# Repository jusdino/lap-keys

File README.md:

# lap-keys
A keyboard design that allows hands to naturally rest on the lap, while using

## Overview
This is a design prototype in progress for a new keyboard that will hopefully fix some ergonomic issues with my desk at home. Namely, I'm sick of keeping my hands up on a desk all day. I'd much rather let them relax on my lap while I work. Nothing I can find for commercially available (or other build-your-own) keyboard/mouse units seem to fit the bill.

## Prototypes
**Split Sixty Wedge**
- This is the first prototype I'm working on that is intended to be 'lap-friendly'. It should receive the custom PCBs I've designed to each include 5 switches in a column and a header that sticks out the top to allow for hand-wiring the key matrix between columns. This prototype is designed to be a simple 5x12 rectilinear split keyboard with each half arranged into a forward-pointing wedge. This configuration should get your wrists into a sensible orientation while typing either on a desk or your lap. It also includes a trackball, to help reduce the need for a dedicated pointing device. I'm calling this first prototype the **split sixty wedge**:

## Prints
The prints section of this repo consists of [OpenScad](https://www.openscad.org/) modules for any prototyping I'm doing and some that allow for quick definition of a keyboard with little more than the coordinates of where you want keys to be located. I've thrown together some *brain_storming* layouts with just coordinates that still produced a part that was reasonably printable, if not polished-looking. 

Some of the OpenScad modules include:

- Any prototypes I'm currently working on
- A rough mock-up of a CherryMX switch:

**Brain storming modules** that can be used for quick brain storming of layout ideas and can potentially be printed out and hand-wired:
- Sockets to fit the CherryMX switch:

- A base to hold the sockets with space underneath for wiring:

- Some utility modules that can take a set of coordinates and translate them into the start of a workable keyboard:

## Firmware
The firmware section of this repo contains MicroController Unit firmware I've designed to run on the MCU that drives the keyboard prototypes. These firmwares use the [QMK firmware](https://qmk.fm/) as their base.

## PCBs
The pcbs section of the repo contains KiCad PCB design files for any PCBs I design as part of this project

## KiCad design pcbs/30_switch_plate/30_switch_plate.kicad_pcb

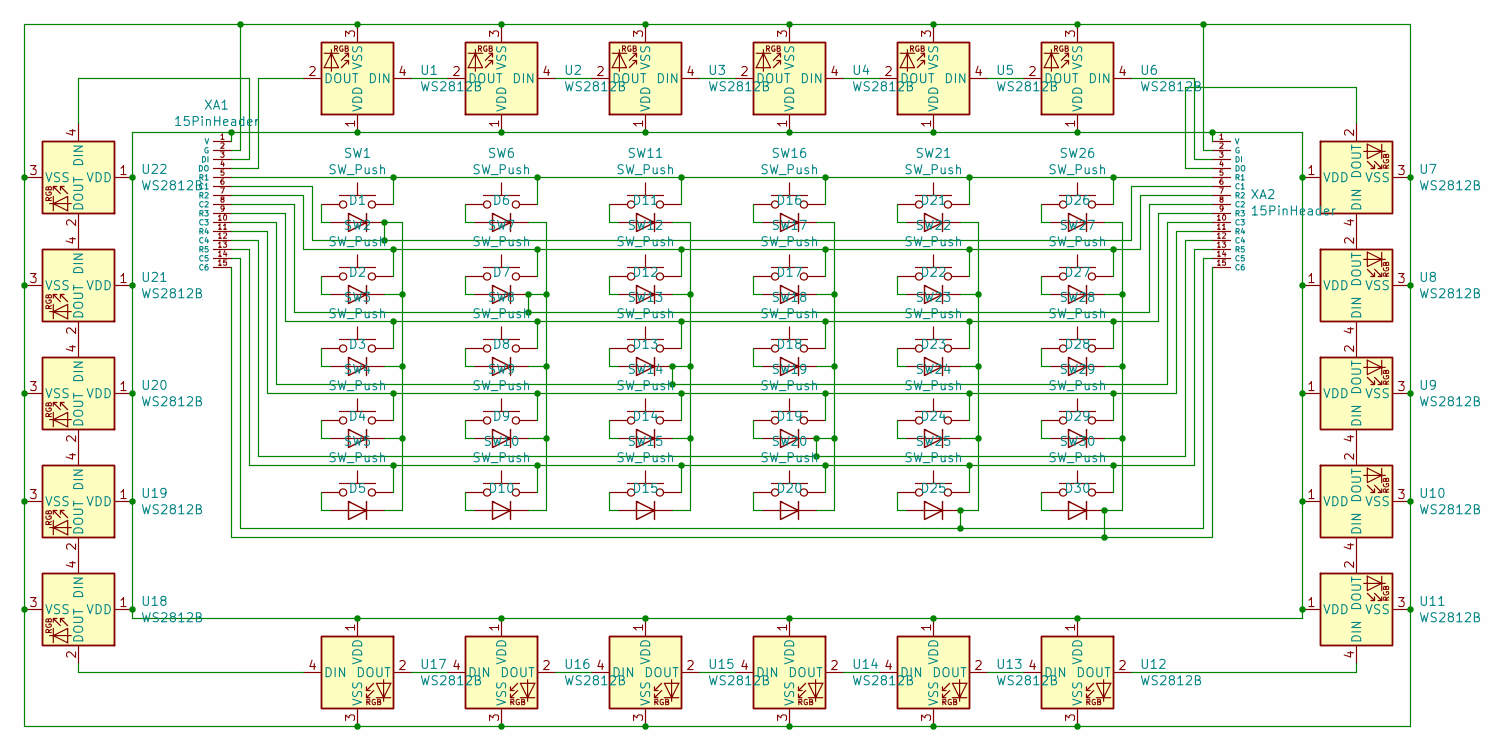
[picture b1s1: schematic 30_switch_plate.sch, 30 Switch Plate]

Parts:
D1, D2, D3, D4, D5, D6, D7, D8, D9, D10, D11, D12, D13, D14, D15, D16, D17, D18, D19, D20, D21, D22, D23, D24, D25, D26, D27, D28, D29, D30: GPDiode; SOD-723; LCSC C308742
SW1, SW2, SW3, SW4, SW5, SW6, SW7, SW8, SW9, SW10, SW11, SW12, SW13, SW14, SW15, SW16, SW17, SW18, SW19, SW20, SW21, SW22, SW23, SW24, SW25, SW26, SW27, SW28, SW29, SW30: SW_Push; SW_Cherry_MX_1.00u_PCB_JF
U1, U2, U3, U4, U5, U6, U7, U8, U9, U10, U11, U12, U13, U14, U15, U16, U17, U18, U19, U20, U21, U22: WS2812B; LED_WS2812B_PLCC4_5.0x5.0mm_P3.2mm; LCSC C114586
XA1, XA2: 15PinHeader

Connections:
unnamed: D1.1 (K), D2.1 (K), D3.1 (K), D4.1 (K), D5.1 (K), XA1.6 (C1), XA2.6 (C1)
unnamed: D1.2 (A), SW1.1
unnamed: D2.2 (A), SW2.1
unnamed: D3.2 (A), SW3.1
unnamed: D4.2 (A), SW4.1
unnamed: D5.2 (A), SW5.1
unnamed: D6.2 (A), SW6.1
unnamed: D7.2 (A), SW7.1
unnamed: D8.2 (A), SW8.1
unnamed: D9.2 (A), SW9.1
unnamed: D6.1 (K), D7.1 (K), D8.1 (K), D9.1 (K), D10.1 (K), XA1.8 (C2), XA2.8 (C2)
unnamed: D10.2 (A), SW10.1
unnamed: D11.1 (K), D12.1 (K), D13.1 (K), D14.1 (K), D15.1 (K), XA1.10 (C3), XA2.10 (C3)
unnamed: D11.2 (A), SW11.1
unnamed: D12.2 (A), SW12.1
unnamed: D13.2 (A), SW13.1
unnamed: D14.2 (A), SW14.1
unnamed: D15.2 (A), SW15.1
unnamed: D16.1 (K), D17.1 (K), D18.1 (K), D19.1 (K), D20.1 (K), XA1.12 (C4), XA2.12 (C4)
unnamed: D16.2 (A), SW16.1
unnamed: D17.2 (A), SW17.1
unnamed: D18.2 (A), SW18.1
unnamed: D19.2 (A), SW19.1
unnamed: D20.2 (A), SW20.1
unnamed: D21.1 (K), D22.1 (K), D23.1 (K), D24.1 (K), D25.1 (K), XA1.14 (C5), XA2.14 (C5)
unnamed: D21.2 (A), SW21.1
unnamed: D22.2 (A), SW22.1
unnamed: D23.2 (A), SW23.1
unnamed: D24.2 (A), SW24.1
unnamed: D25.2 (A), SW25.1
unnamed: D26.1 (K), D27.1 (K), D28.1 (K), D29.1 (K), D30.1 (K), XA1.15 (C6), XA2.15 (C6)
unnamed: D26.2 (A), SW26.1
unnamed: D27.2 (A), SW27.1
unnamed: D28.2 (A), SW28.1
unnamed: D29.2 (A), SW29.1
unnamed: D30.2 (A), SW30.1
unnamed: SW1.2, SW6.2, SW11.2, SW16.2, SW21.2, SW26.2, XA1.5 (R1), XA2.5 (R1)
unnamed: SW5.2, SW10.2, SW15.2, SW20.2, SW25.2, SW30.2, XA1.13 (R5), XA2.13 (R5)
unnamed: SW2.2, SW7.2, SW12.2, SW17.2, SW22.2, SW27.2, XA1.7 (R2), XA2.7 (R2)
unnamed: SW3.2, SW8.2, SW13.2, SW18.2, SW23.2, SW28.2, XA1.9 (R3), XA2.9 (R3)
unnamed: SW4.2, SW9.2, SW14.2, SW19.2, SW24.2, SW29.2, XA1.11 (R4), XA2.11 (R4)
unnamed: U1.1 (VDD), U2.1 (VDD), U3.1 (VDD), U4.1 (VDD), U5.1 (VDD), U6.1 (VDD), U7.1 (VDD), U8.1 (VDD), U9.1 (VDD), U10.1 (VDD), U11.1 (VDD), U12.1 (VDD), U13.1 (VDD), U14.1 (VDD), U15.1 (VDD), U16.1 (VDD), U17.1 (VDD), U18.1 (VDD), U19.1 (VDD), U20.1 (VDD), U21.1 (VDD), U22.1 (VDD), XA1.1 (V), XA2.1 (V)
unnamed: U1.2 (DOUT), XA1.4 (DO)
unnamed: U1.3 (VSS), U2.3 (VSS), U3.3 (VSS), U4.3 (VSS), U5.3 (VSS), U6.3 (VSS), U7.3 (VSS), U8.3 (VSS), U9.3 (VSS), U10.3 (VSS), U11.3 (VSS), U12.3 (VSS), U13.3 (VSS), U14.3 (VSS), U15.3 (VSS), U16.3 (VSS), U17.3 (VSS), U18.3 (VSS), U19.3 (VSS), U20.3 (VSS), U21.3 (VSS), U22.3 (VSS), XA1.2 (G), XA2.2 (G)
unnamed: U1.4 (DIN), U2.2 (DOUT)
unnamed: U2.4 (DIN), U3.2 (DOUT)
unnamed: U3.4 (DIN), U4.2 (DOUT)
unnamed: U4.4 (DIN), U5.2 (DOUT)
unnamed: U5.4 (DIN), U6.2 (DOUT)
unnamed: U6.4 (DIN), XA2.3 (DI)
unnamed: U7.2 (DOUT), XA2.4 (DO)
unnamed: U7.4 (DIN), U8.2 (DOUT)
unnamed: U8.4 (DIN), U9.2 (DOUT)
unnamed: U9.4 (DIN), U10.2 (DOUT)
unnamed: U10.4 (DIN), U11.2 (DOUT)
unnamed: U11.4 (DIN), U12.2 (DOUT)
unnamed: U12.4 (DIN), U13.2 (DOUT)
unnamed: U13.4 (DIN), U14.2 (DOUT)
unnamed: U14.4 (DIN), U15.2 (DOUT)
unnamed: U15.4 (DIN), U16.2 (DOUT)
unnamed: U16.4 (DIN), U17.2 (DOUT)
unnamed: U17.4 (DIN), U18.2 (DOUT)
unnamed: U18.4 (DIN), U19.2 (DOUT)
unnamed: U19.4 (DIN), U20.2 (DOUT)
unnamed: U20.4 (DIN), U21.2 (DOUT)
unnamed: U21.4 (DIN), U22.2 (DOUT)
unnamed: U22.4 (DIN), XA1.3 (DI)

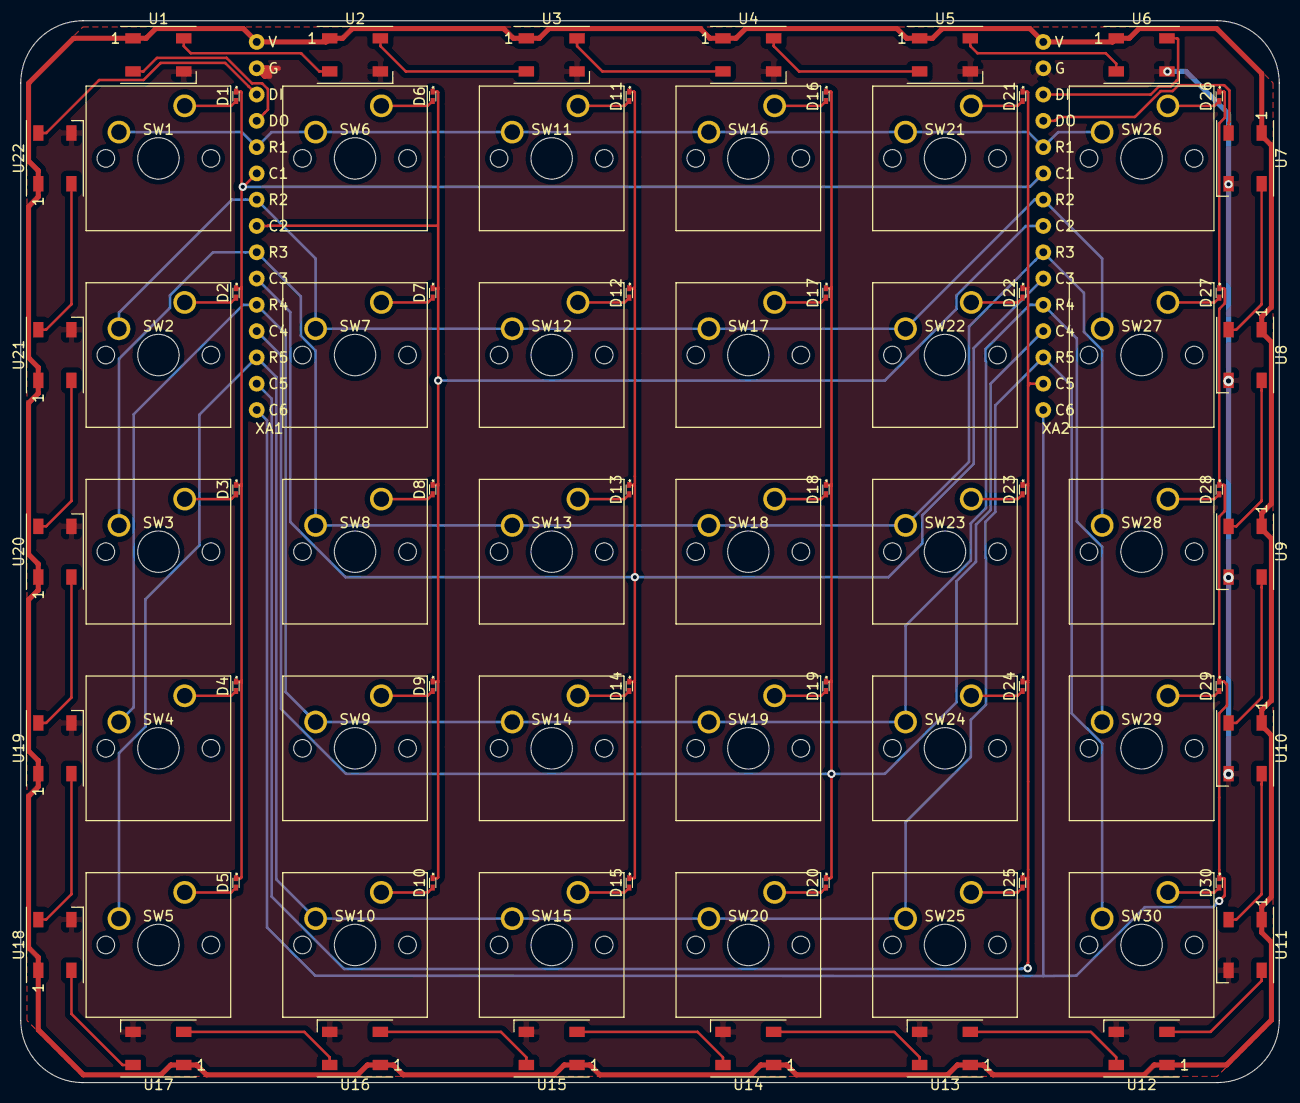
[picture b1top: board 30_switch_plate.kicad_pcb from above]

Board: 2 copper layers, 121.6 x 102.6 mm, 84 parts (0 on the bottom side), 67 nets.

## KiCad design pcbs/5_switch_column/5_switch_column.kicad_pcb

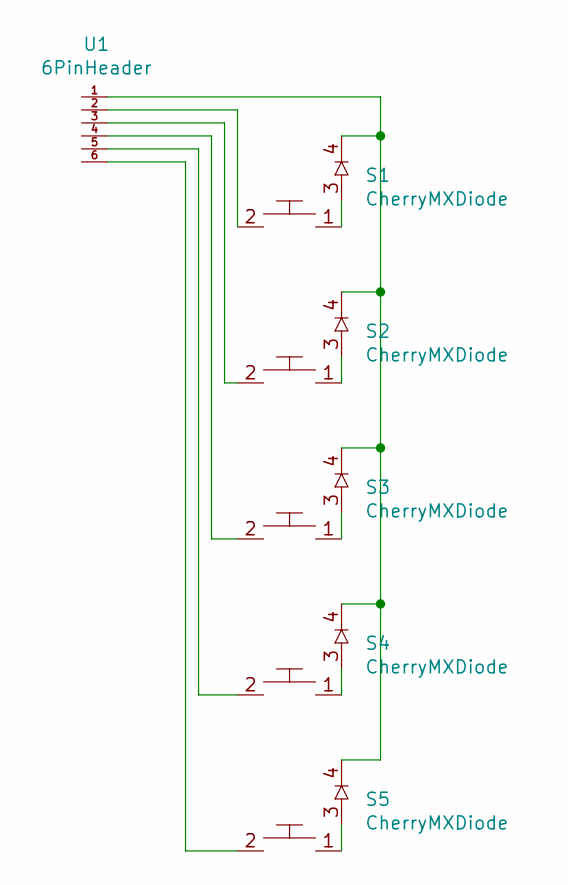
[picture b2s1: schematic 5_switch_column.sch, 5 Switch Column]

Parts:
S1, S2, S3, S4, S5: CherryMXDiode; SW_Cherry_MX_1.00u_PCB
U1: 6PinHeader

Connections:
unnamed: S1.1, S1.3
unnamed: S1.2, U1.2
unnamed: S1.4, S2.4, S3.4, S4.4, S5.4, U1.1
unnamed: S2.1, S2.3
unnamed: S2.2, U1.3
unnamed: S3.1, S3.3
unnamed: S3.2, U1.4
unnamed: S4.1, S4.3
unnamed: S4.2, U1.5
unnamed: S5.1, S5.3
unnamed: S5.2, U1.6

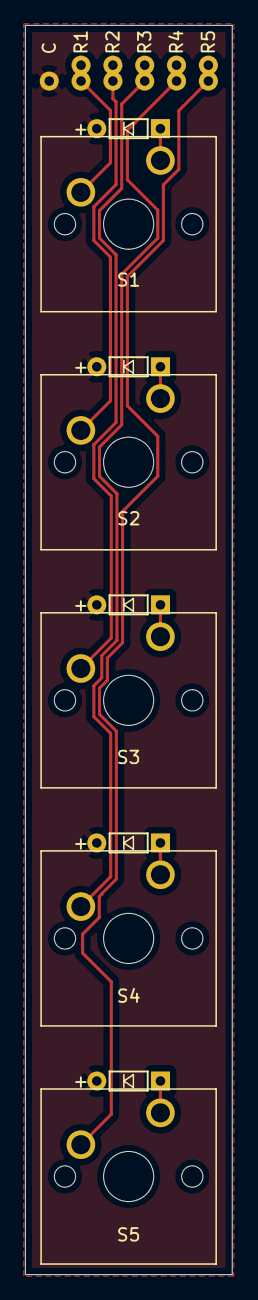
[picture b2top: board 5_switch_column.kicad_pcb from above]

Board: 2 copper layers, 16.5 x 99.7 mm, 6 parts (0 on the bottom side), 11 nets.

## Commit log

2020-05-17 Add a couple starting files
2020-05-17 Add some layouts
2020-05-17 Create LICENSE
2020-05-17 fix typos
2020-05-17 Refine some geometry details
2020-05-17 Update screenshot
2020-05-21 Add a quick-and-dirty base
2020-05-23 Add some outputs, firmware, updated README notes
2020-05-31 Add split sixty wedge
2020-06-04 Some minor keymap tweaks
2020-06-09 Update split sixty wedge
2020-06-09 Adding some transparent keys in layer 1
2020-06-10 Drop duplicate files
2020-06-12 trackball - break everything
2020-06-12 Well, it compiles now
2020-06-12 Fixed v0.1 files
2020-06-18 Shift a keymap row
2020-07-18 Update pins, try adding debug
2020-07-18 Futzing
2020-07-19 Progress?
2020-07-19 Super broken but commiting anyway
2020-07-20 At lest the keys work now...
2020-07-22 I have no idea what I'm doing
2020-07-26 comms good, SROM bad
2020-07-27 Holy crap, it works!
2020-07-27 Drop debug key
2020-07-28 Make it all work!
2020-07-28 Make SPI work (#2)
    * comms good, SROM bad
    * Holy crap, it works!
    * Drop debug key
    * Make it all work!
2020-07-28 Clean up some debugging
2020-07-28 Update to use spi_master.h driver
2020-07-28 Clean up dead code
2020-07-28 Qmk spi master driver (#3)
    * Clean up some debugging
    * Update to use spi_master.h driver
    * Clean up dead code
2020-07-28 Some tweaks from Drashna's feedback
2020-08-02 Add some READMEs
2020-08-04 Add KiCAD PCB files
2020-08-07 Add a broken Proton-C firmware
2020-08-07 Drop api_sysex and it compiles
2020-08-07 Tweaks per feedback from tzarc
2020-08-07 api_sysex=BAD IDEA
2020-08-07 Firmware cleanup
2020-08-09 Split_Sixty_Wedge w/ PCB in prog
2020-08-09 Some minor cleanup
2020-08-09 Clean up these stinking projec files _again_
2020-08-10 Add beginings of the base
2020-08-12 Finish ss wedge, cleanup
2020-08-14 Revisions after first print
2020-08-16 Some variable/module organizing
2020-08-19 Begin mcu-mount design
2020-08-20 Add Elite C mount
2020-08-20 Update pins used
2020-08-30 Reorg, start trackball mount
2020-09-02 Attach trackball mount to kb base
2020-09-03 Add trackball mount backing
2020-09-20 Add mouse-keys layer
2020-09-20 Revise trackball design to one that actually worked
2020-09-20 Tune trackball sensitivity
2020-11-04 Add 30_switch_plate
2020-11-18 Update plates for 30_switch_plate
2020-11-22 Adapt prints for 30_switch_plate
2020-11-24 Some post-production tweaks
2021-02-08 Turn ws2812b orientation around
2021-07-16 fillet base connectors
2022-08-14 Move to pin-tab mcu connectors
2023-04-16 Fully enclosed base

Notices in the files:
pcbs/30_switch_plate/30_switch_plate.kicad_pcb:
License: GPL v3
pcbs/30_switch_plate/30_switch_plate.sch:
https://www.gnu.org/licenses/gpl-3.0.html
